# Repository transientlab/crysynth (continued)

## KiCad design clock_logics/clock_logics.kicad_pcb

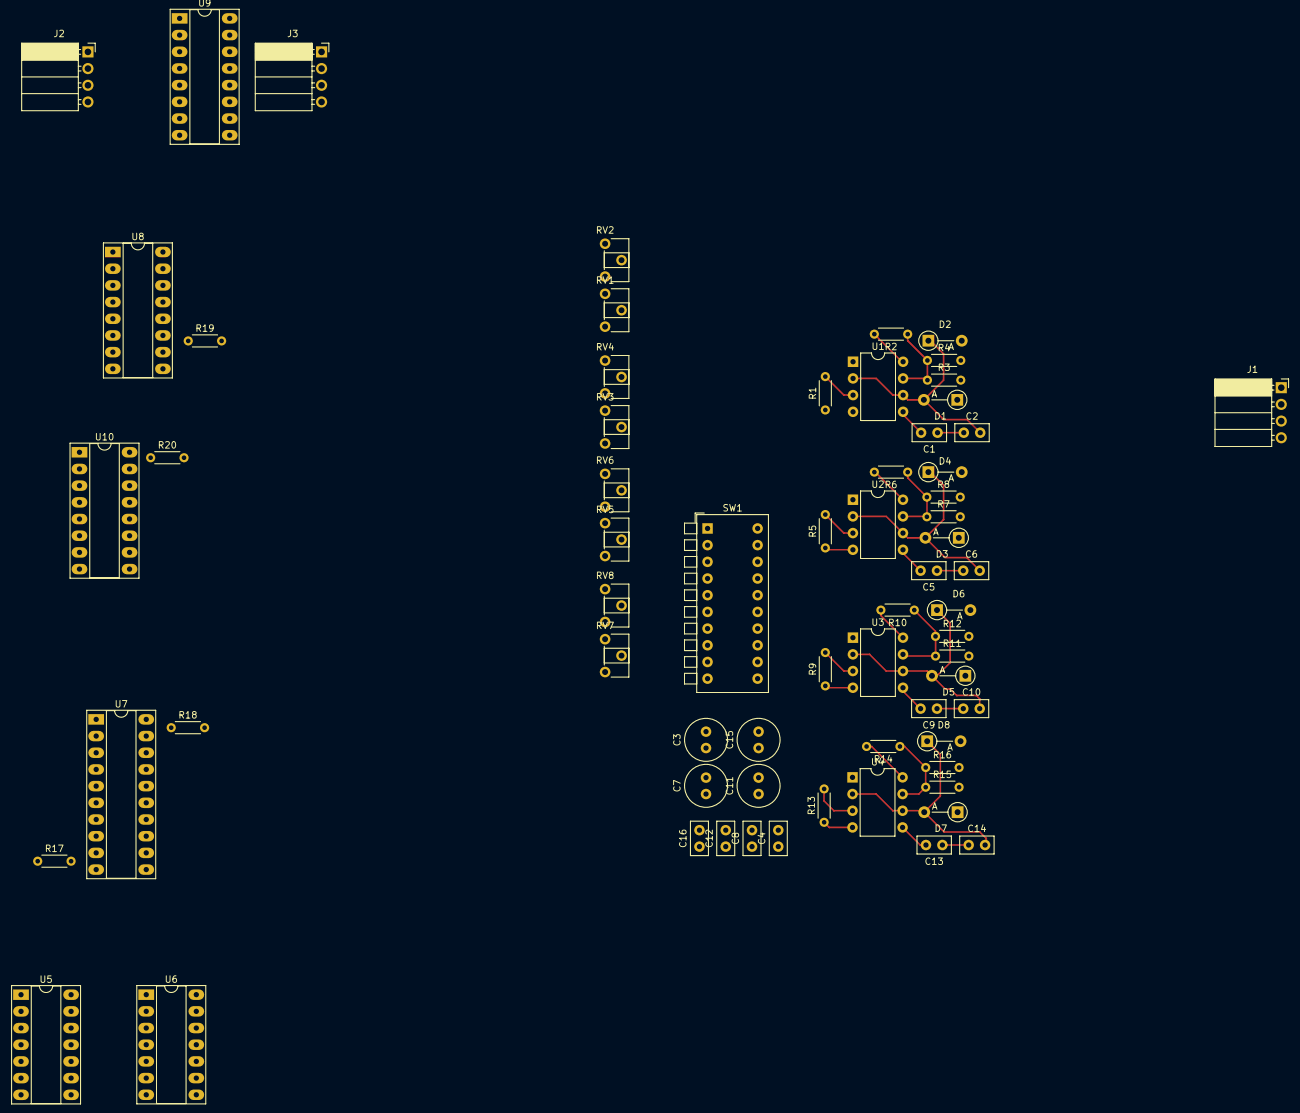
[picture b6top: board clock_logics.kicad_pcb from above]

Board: 2 copper layers, 66 parts (0 on the bottom side), 54 nets.

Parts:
C1, C2, C4, C5, C6, C8, C9, C10, C12, C13, C14, C16: C; C_Disc_D5.0mm_W2.5mm_P2.50mm
C3, C7, C11, C15: C; C_Radial_D6.3mm_H11.0mm_P2.50mm
D1, D2, D3, D4, D5, D6, D7, D8: D; D_A-405_P5.08mm_Vertical_AnodeUp
J1, J2, J3: Conn_01x04_Male; PinSocket_1x04_P2.54mm_Horizontal
R1, R2, R5, R6, R9, R10, R13, R14, R17, R18, R19, R20: 1k; R_Axial_DIN0204_L3.6mm_D1.6mm_P5.08mm_Horizontal
R3, R4, R7, R8, R11, R12, R15, R16: 10; R_Axial_DIN0204_L3.6mm_D1.6mm_P5.08mm_Horizontal
RV1, RV2, RV3, RV4, RV5, RV6, RV7, RV8: R_Potentiometer; Potentiometer_Piher_PT-6-H_Horizontal
SW1: SW_DIP_x10; SW_DIP_SPSTx10_Piano_10.8x26.96mm_W7.62mm_P2.54mm
U1, U2, U3, U4: NE555P; DIP-8_W7.62mm
U5: 4011; DIP-14_W7.62mm_Socket_LongPads
U6: 4001; DIP-14_W7.62mm_Socket_LongPads
U7: 74HC240; DIP-20_W7.62mm_Socket_LongPads
U8: 4020; DIP-16_W7.62mm_Socket_LongPads
U9: 4076; DIP-16_W7.62mm_Socket_LongPads
U10: 4017; DIP-16_W7.62mm_Socket_LongPads

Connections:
+5V: R1.1, R2.2, R5.1, R6.2, R9.1, R10.2, R13.1, R14.2, U1.4 (R), U1.8 (VCC), U2.4 (R), U2.8 (VCC), U3.4 (R), U3.8 (VCC), U4.4 (R), U4.8 (VCC), U5.14 (VDD), U6.14 (VDD), U7.20 (VCC), U8.16 (VDD), U10.16 (VDD)
/clk1out: J1.1, R1.2, U1.3 (Q)
/clk2out: J1.2, R5.2, U2.3 (Q)
/clk3out: J1.3, R9.2, U3.3 (Q)
/clk4out: J1.4, R13.2, U4.3 (Q)
/ct1: C2.2, D1.2 (A), D2.1 (K), SW1.1, SW1.2, U1.2 (TR), U1.6 (THR)
/ct2: C6.2, D3.2 (A), D4.1 (K), SW1.3, SW1.4, U2.2 (TR), U2.6 (THR)
/ct3: C10.2, D5.2 (A), D6.1 (K), SW1.5, SW1.6, U3.2 (TR), U3.6 (THR)
/ct4: C14.2, D7.2 (A), D8.1 (K), SW1.7, SW1.8, U4.2 (TR), U4.6 (THR)
GND: C1.1, C2.1, C3.1, C4.1, C5.1, C6.1, C7.1, C8.1, C9.1, C10.1, C11.1, C12.1, C13.1, C14.1, C15.1, C16.1, R17.2, R18.2, R19.2, R20.2, U1.1 (GND), U2.1 (GND), U3.1 (GND), U4.1 (GND), U5.7 (VSS), U6.7 (VSS), U7.10 (GND), U8.8 (VSS), U9.1 (M), U9.2 (N), U9.8 (GND), U9.9 (G1), U9.10 (G2), U9.15 (Reset), U10.8 (VSS), U10.13 (CKEN)
unnamed: C1.2, U1.5 (CV)
unnamed: C5.2, U2.5 (CV)
unnamed: C8.2, SW1.17
unnamed: C9.2, U3.5 (CV)
unnamed: C13.2, U4.5 (CV)
unnamed: D1.1 (K), RV1.3
unnamed: D2.2 (A), RV2.1, RV2.2
unnamed: D3.1 (K), RV3.3
unnamed: D4.2 (A), RV4.1, RV4.2
unnamed: D5.1 (K), RV5.3
unnamed: D6.2 (A), RV6.1, RV6.2
unnamed: D7.1 (K), RV7.3
unnamed: D8.2 (A), RV8.1, RV8.2
unnamed: J2.1, U9.3 (D1)
unnamed: J2.2, U9.4 (D2)
unnamed: J2.3, U9.5 (D3)
unnamed: J2.4, U9.6 (D4)
unnamed: J3.1, U9.14 (Q1)
unnamed: J3.2, U9.13 (Q2)
unnamed: J3.3, U9.12 (Q3)
unnamed: J3.4, U9.11 (Q4)
unnamed: R2.1, R3.1, R4.1, U1.7 (DIS)
unnamed: R3.2, RV1.1, RV1.2
unnamed: R4.2, RV2.3
unnamed: R6.1, R7.1, R8.1, U2.7 (DIS)
unnamed: R7.2, RV3.1, RV3.2
unnamed: R8.2, RV4.3
unnamed: R10.1, R11.1, R12.1, U3.7 (DIS)
unnamed: R11.2, RV5.1, RV5.2
unnamed: R12.2, RV6.3
unnamed: R14.1, R15.1, R16.1, U4.7 (DIS)
unnamed: R15.2, RV7.1, RV7.2
unnamed: R16.2, RV8.3
unnamed: R17.1, U7.1 (1OE)
unnamed: R18.1, U7.19 (2OE)
unnamed: R19.1, U8.11 (Reset)
unnamed: R20.1, U10.15 (Reset)
unnamed: C16.2, SW1.13
unnamed: C15.2, SW1.14
unnamed: C12.2, SW1.15
unnamed: C11.2, SW1.16
unnamed: C7.2, SW1.18
unnamed: C4.2, SW1.19
unnamed: C3.2, SW1.20

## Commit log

2022-11-01 RAW files added
2022-11-01 plt, log - ltspice
2022-11-01 DS_Store clean ignore
2022-11-01 add DS_Store
2022-11-01 KiCAD backups, autosaves
2022-11-01 checking
2022-11-27 3 phase rectifier
2022-11-29 old analogs
2022-11-29 trnst_a
2022-12-02 clock_logics
2022-12-02 new schematics
2022-12-04 ok new boards 110x42 logics
2022-12-04 move template
2022-12-07 vcf_ba6110
2022-12-11 voltage bias
2022-12-19 new projects
2022-12-20 SEQUENCER auto_saved_files
2022-12-20 something
2022-12-22 relay kicad_pcb
2023-02-24 m4base
2023-03-01 m4 base
2023-08-22 opened project
2023-08-29 antialias
2023-09-02 opeinig
2023-12-23 new kicad
2023-12-29 new board
2024-07-05 review
